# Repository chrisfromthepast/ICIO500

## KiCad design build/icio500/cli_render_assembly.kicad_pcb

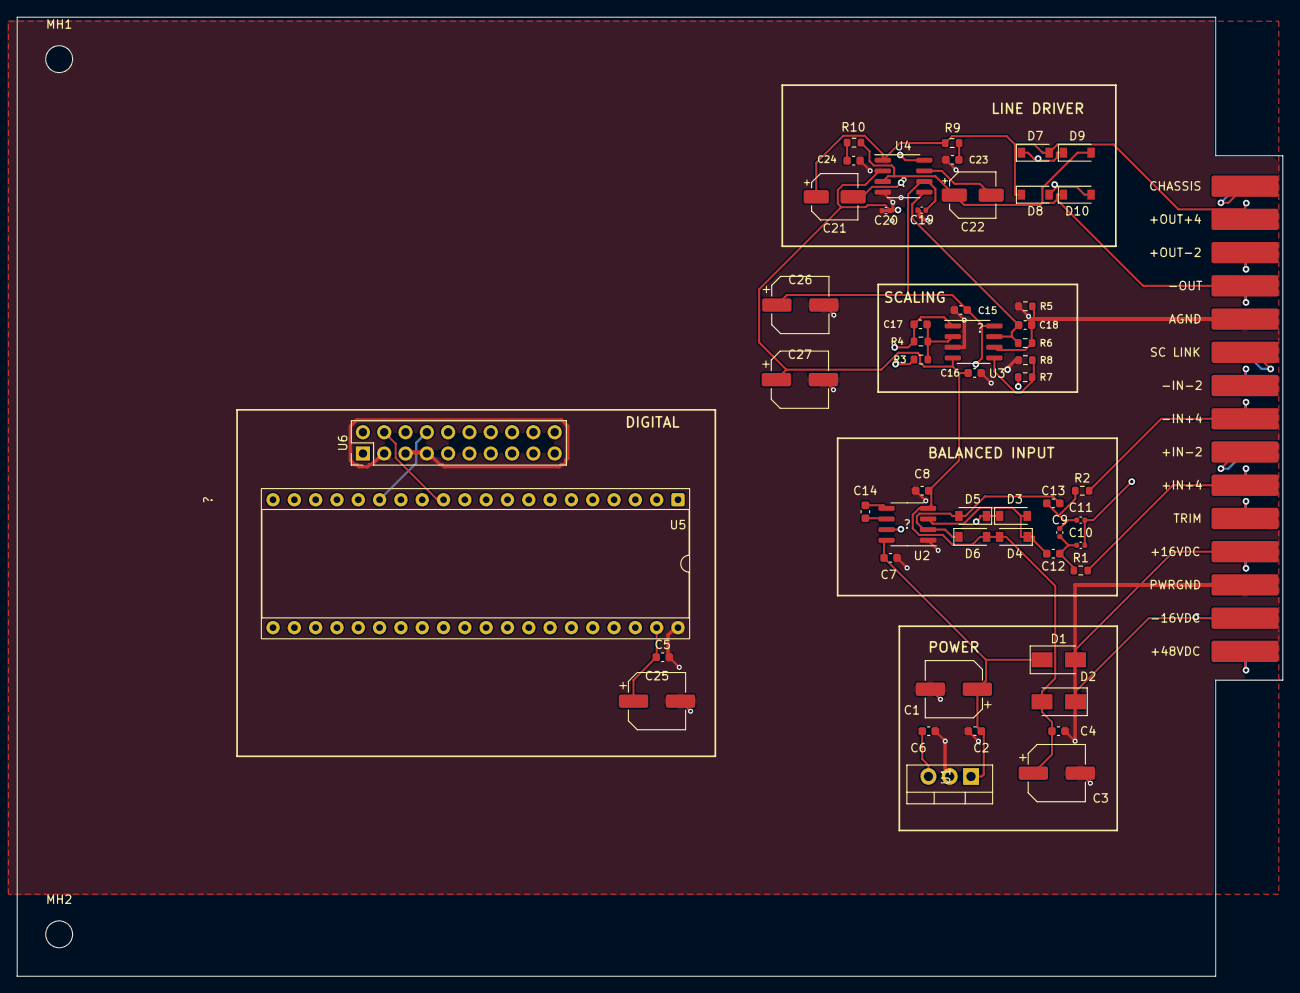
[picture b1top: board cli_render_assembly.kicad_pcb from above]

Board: 4 copper layers, 150.8 x 114.3 mm, 56 parts (0 on the bottom side), 41 nets.

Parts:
C1, C3, C25, C26, C27: ?; CP_Elec_6.3x5.4
C2, C4, C5, C6, C7, C8, C12, C13, C14, C15, C16, C17, C18, C23, C24: C0603
C9, C10, C11, C19, C20: C0402
C21, C22: ?; CP_Elec_5x5.4
D1, D2: ?; D_SMA
D3, D4, D5, D6, D7, D8, D9, D10: ?; D_SOD-123
J1: ?; EDA_306
MH1, MH2: MountingHole_3.2mm_M3
R1, R2, R3, R4, R5, R6, R7, R8, R9, R10: R0603
U1: ?; TO-220-3_Vertical
U2, U3, U4: ?; SOIC-8_3.9x4.9mm_P1.27mm
U5: ?; DIP-40_W15.24mm_Socket
U6: ?; PinHeader_2x10_P2.54mm_Vertical

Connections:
audio_in_from_daisy_plus: R7.1, U5.35
audio_in_r: U5.38, U6.2
audio_out: R3.1, U2.7
audio_out_to_1646: C18.1, R6.1, U3.7, U4.5
chassis_gnd: C10.2, C11.2, J1.1
cm: C14.1, U2.6
d13: U5.15, U6.8
d14: U5.16, U6.9
daisy_5v_power: C5.1, C6.1, C25.1, U1.3, U5.39, U6.1
daisy_audio_in: C17.1, R4.1, U3.1, U5.37
driver.r_zobel_minus-vcc: C24.1, R10.2
driver.r_zobel_plus-vcc: C23.1, R9.2
gnd: C1.2, C2.2, C3.2, C4.2, C5.2, C6.2, C7.2, C8.2, C15.2, C16.2, C19.2, C20.2, C23.2, C24.2, C25.2, C26.2, C27.2, J1.5, J1.13, R5.1, R8.1, U1.2, U2.1, U3.3, U4.4, U5.40, U6.3, U6.5, U6.7
gpio_disp_dc: U5.6, U6.16
gpio_disp_res: U5.5, U6.17
gpio_enc_b: U5.17, U6.10
gpio_enc_sw: U5.18, U6.11
i2c1_scl: U5.11, U6.6
i2c1_sda: U5.12, U6.4
in_minus: C13.2, D5.2, D6.1, U2.2
in_minus_1: C17.2, R3.2, R4.2, U3.2
in_minus_2: C18.2, R5.2, R6.2, U3.6
in_minus_4dbu: J1.8, R2.1
in_plus: C12.2, D3.2, D4.1, U2.3
in_plus_2: R7.2, R8.2, U3.5
in_plus_4dbu: J1.10, R1.1
out_minus: C22.1, D9.2, D10.1, J1.4, R10.1, U4.3
out_plus_4dbu: C21.1, D7.2, D8.1, J1.2, R9.1, U4.1
receiver.r_rf_minus-vcc: C9.2, C11.1, C13.1, R2.2
receiver.r_rf_plus-vcc: C9.1, C10.1, C12.1, R1.2
sense_minus: C22.2, U4.7
sense_plus: C21.2, U4.8
sm: C14.2, U2.5
spi1_cs: U5.7, U6.15
spi1_miso: U5.9, U6.13
spi1_mosi: U5.10, U6.12
spi1_sck: U5.8, U6.14
v_minus: C3.1, C4.1, C8.1, C16.1, C20.1, C27.1, D2.2, D4.2, D6.2, D8.2, D10.2, U2.4, U3.4, U4.2
v_minus_16v: D2.1, J1.14
v_plus: C1.1, C2.1, C7.1, C15.1, C19.1, C26.1, D1.1, D3.1, D5.1, D7.1, D9.1, U1.1, U2.8, U3.8, U4.6
v_plus_16v: D1.2, J1.12
